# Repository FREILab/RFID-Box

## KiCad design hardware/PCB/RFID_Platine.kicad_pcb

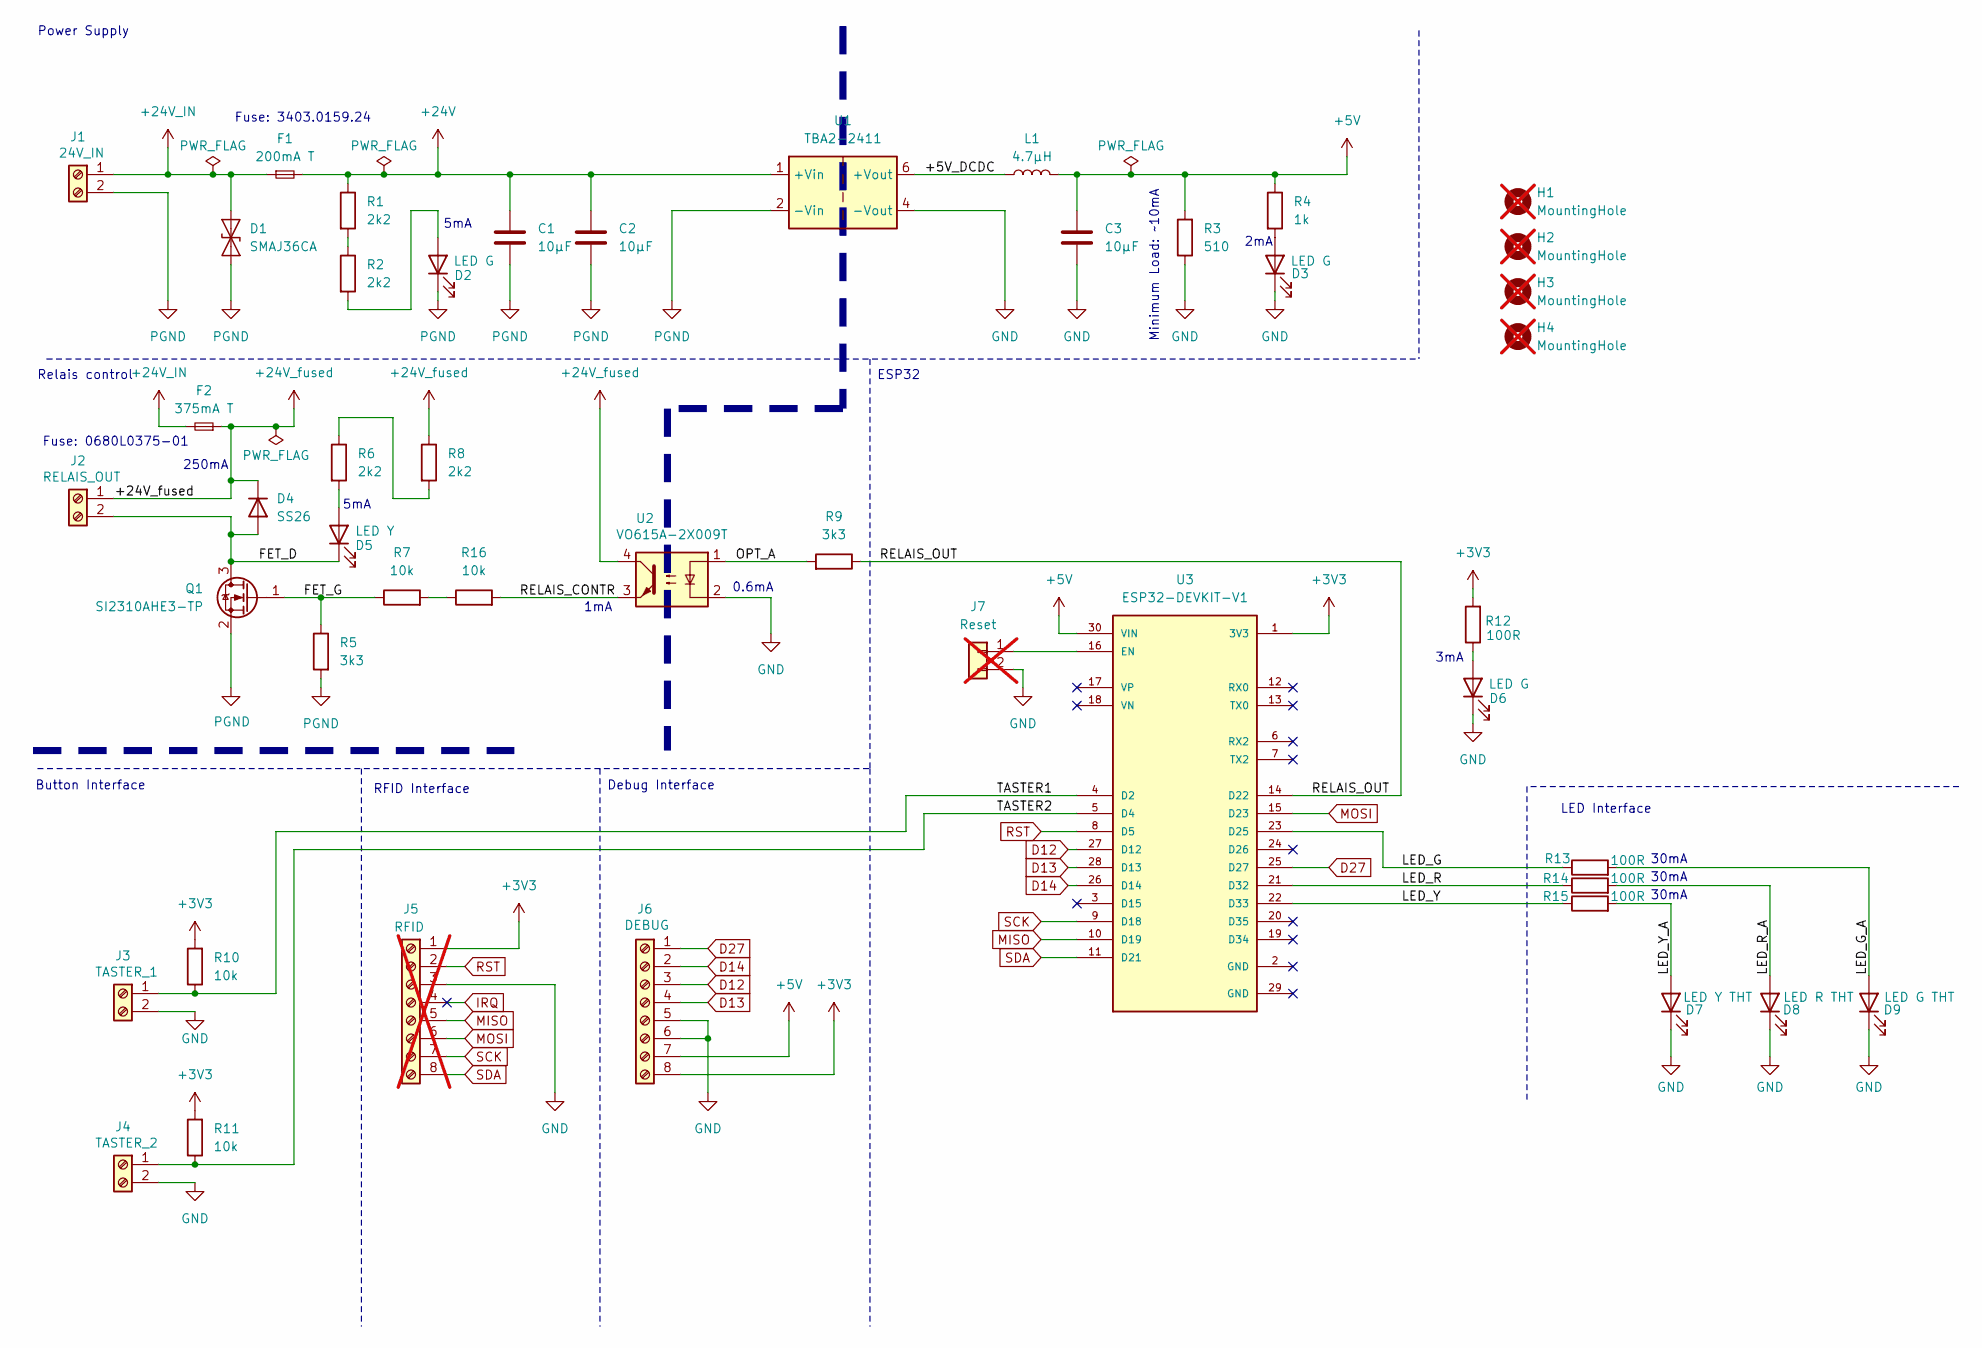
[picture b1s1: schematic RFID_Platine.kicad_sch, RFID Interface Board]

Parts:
C1, C2, C3: 10µF; C_0805_2012Metric; Voltage Rating 50V; Digikey 490-GRM21BR61H106KE43KCT-ND
D1: SMAJ36CA; D_SMA; Digikey SMAJ36CA-TPMSCT-ND
D2, D3, D6: LED G; LED_0603_1608Metric; Digikey 160-1183-1-ND
D4: SS26; D_SMA; Digikey SS26-LTPMSCT-ND
D5: LED Y; LED_0603_1608Metric; Digikey 160-1448-1-ND
D7: LED Y THT; LED_D5.0mm_Horizontal_O6.35mm_Z15.0mm; Digikey 1516-1362-ND
D8: LED R THT; LED_D5.0mm_Horizontal_O6.35mm_Z15.0mm; Digikey 1516-1359-ND
D9: LED G THT; LED_D5.0mm_Horizontal_O6.35mm_Z15.0mm; Digikey 1516-1364-ND
F1: 200mA T; Fuse_Schurter_UMZ250; Digikey 486-4658-1-ND
F2: 375mA T; Fuse_Littelfuse-NANO2-451_453; Digikey 5923-0680L0375-01CT-ND
H1, H2, H3, H4: MountingHole; MountingHole_4mm; not fitted
J1: 24V_IN; TerminalBlock_Phoenix_PT-1,5-2-3.5-H_1x02_P3.50mm_Horizontal; Digikey 277-1721-ND
J2: RELAIS_OUT; TerminalBlock_Phoenix_PT-1,5-2-3.5-H_1x02_P3.50mm_Horizontal; Digikey 277-1721-ND
J3: TASTER_1; TerminalBlock_Phoenix_PT-1,5-2-3.5-H_1x02_P3.50mm_Horizontal; Digikey 277-1721-ND
J4: TASTER_2; TerminalBlock_Phoenix_PT-1,5-2-3.5-H_1x02_P3.50mm_Horizontal; Digikey 277-1721-ND
J5: RFID; PinHeader_1x08_P2.54mm_Vertical; not fitted
J6: DEBUG; PinHeader_1x08_P2.54mm_Vertical
J7: Reset; PinHeader_1x02_P2.54mm_Vertical; not fitted
L1: 4.7µH; L_Chilisin_BMRB00060650; Digikey 445-174746-1-ND
Q1: SI2310AHE3-TP; SOT-23; Digikey 353-SI2310AHE3-TP-ND
R1, R2, R6, R8: 2k2; R_0603_1608Metric; Power Rating 100mW; Digikey 13-RC0603FR-132K2LCT-ND
R3: 510; R_0603_1608Metric; Power Rating 100mW; Digikey 311-510HRCT-ND
R4: 1k; R_0603_1608Metric; Power Rating 100mW; Digikey 311-1.00KHRCT-ND
R5, R9: 3k3; R_0603_1608Metric; Power Rating 100mW; Digikey 311-3.30KHRCT-ND
R7, R10, R11, R16: 10k; R_0603_1608Metric; Power Rating 100mW; Digikey 311-10.0KHRCT-ND
R12, R13, R14, R15: 100R; R_0805_2012Metric; Power Rating 125mW; Digikey 311-100CRCT-ND
U1: TBA2-2411; Converter_DCDC_TRACO_TBA2-xxxx_Single_THT; Digikey 1951-3441-ND
U2: VO615A-2X009T; DIP-4_W8.89mm_SMDSocket_LongPads; Digikey VO615A-2X009TCT-ND
U3: ESP32-DEVKIT-V1; MODULE_ESP32_DEVKIT_V1; PARTREV N/A

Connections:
+3V3: J5.1, J6.8, R10.2, R11.2, R12.2, U3.1 (3V3)
+5V: C3.1, J6.7, L1.2, R3.2, R4.1, U3.30 (VIN)
+24V: C1.1, C2.1, F1.2, R1.1, U1.1 (+Vin)
+24V_IN: D1.2 (A2), F1.1, F2.2, J1.1
+24V_fused: D4.1 (K), F2.1, J2.1, R8.1, U2.4
/+5V_DCDC: L1.1, U1.6 (+Vout)
/FET_D: D4.2 (A), D5.1 (K), J2.2, Q1.3 (D)
/FET_G: Q1.1 (G), R5.1, R7.1
/LED_G: R13.1, U3.23 (D25)
/LED_G_A: D9.2 (A), R13.2
/LED_R: R14.1, U3.21 (D32)
/LED_R_A: D8.2 (A), R14.2
/LED_Y: R15.1, U3.22 (D33)
/LED_Y_A: D7.2 (A), R15.2
/OPT_A: R9.2, U2.1
/RELAIS_CONTR: R16.2, U2.3
/RELAIS_OUT: R9.1, U3.14 (D22)
/TASTER1: J3.1, R10.1, U3.4 (D2)
/TASTER2: J4.1, R11.1, U3.5 (D4)
D12: J6.3, U3.27 (D12)
D13: J6.4, U3.28 (D13)
D14: J6.2, U3.26 (D14)
D27: J6.1, U3.25 (D27)
GND: C3.2, D3.1 (K), D6.1 (K), D7.1 (K), D8.1 (K), D9.1 (K), J3.2, J4.2, J5.3, J6.5, J6.6, J7.2, R3.1, U1.4 (-Vout), U2.2
IRQ: J5.4
MISO: J5.5, U3.10 (D19)
MOSI: J5.6, U3.15 (D23)
unnamed: D2.2 (A), R2.2
unnamed: D3.2 (A), R4.2
unnamed: D5.2 (A), R6.2
unnamed: D6.2 (A), R12.1
unnamed: J7.1, U3.16 (EN)
unnamed: R1.2, R2.1
unnamed: R6.1, R8.2
unnamed: R7.2, R16.1
PGND: C1.2, C2.2, D1.1 (A1), D2.1 (K), J1.2, Q1.2 (S), R5.2, U1.2 (-Vin)
RST: J5.2, U3.8 (D5)
SCK: J5.7, U3.9 (D18)
SDA: J5.8, U3.11 (D21)

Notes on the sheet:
2mA
30mA
Fuse: 3403.0159.24
RFID Interface
LED Interface
5mA
0.6mA
Relais control
1mA
3mA
Debug Interface
Button Interface
250mA
ESP32
Power Supply
Fuse: 0680L0375-01
Minimum Load: ~10mA

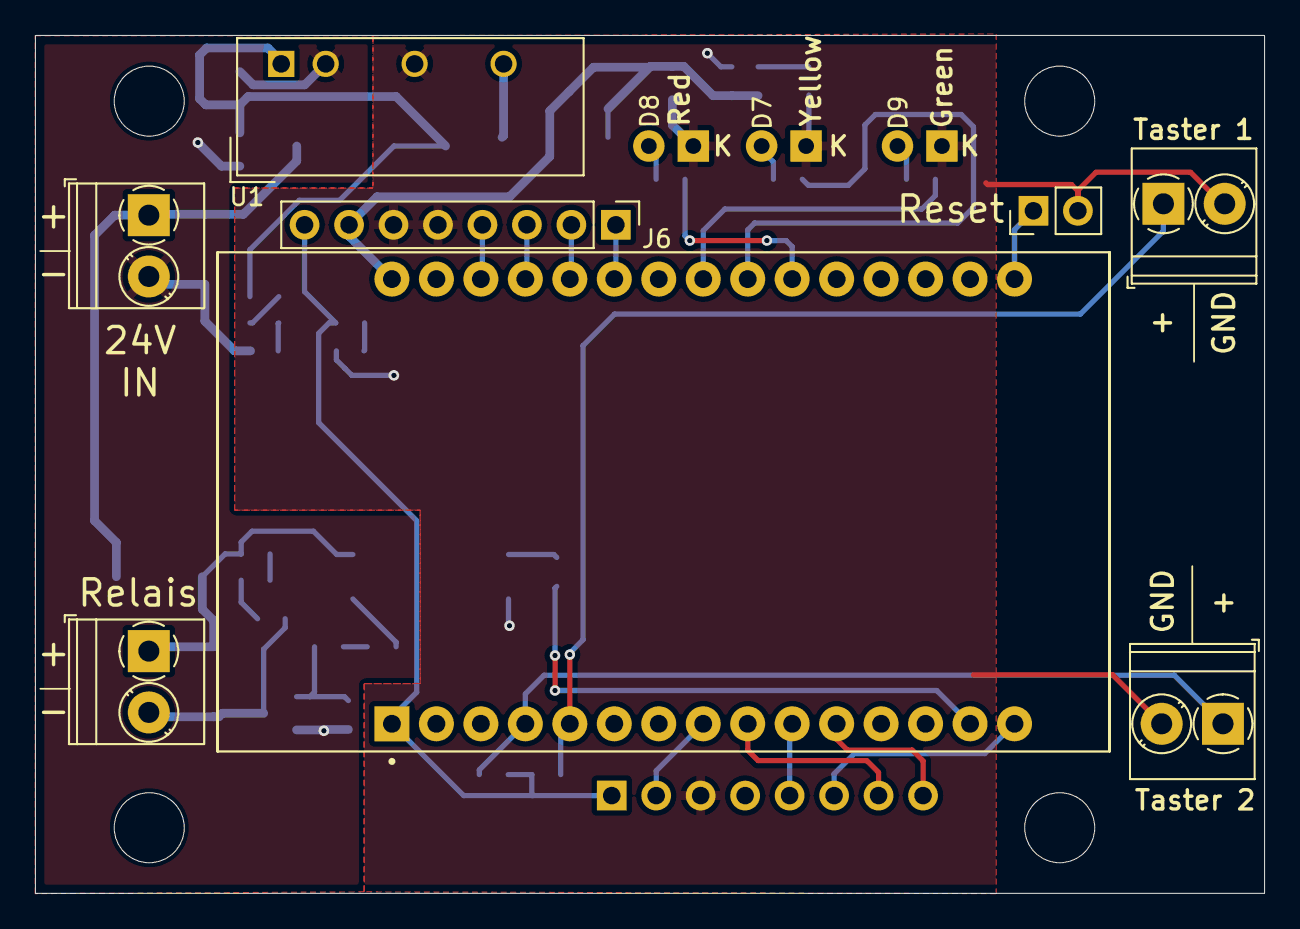
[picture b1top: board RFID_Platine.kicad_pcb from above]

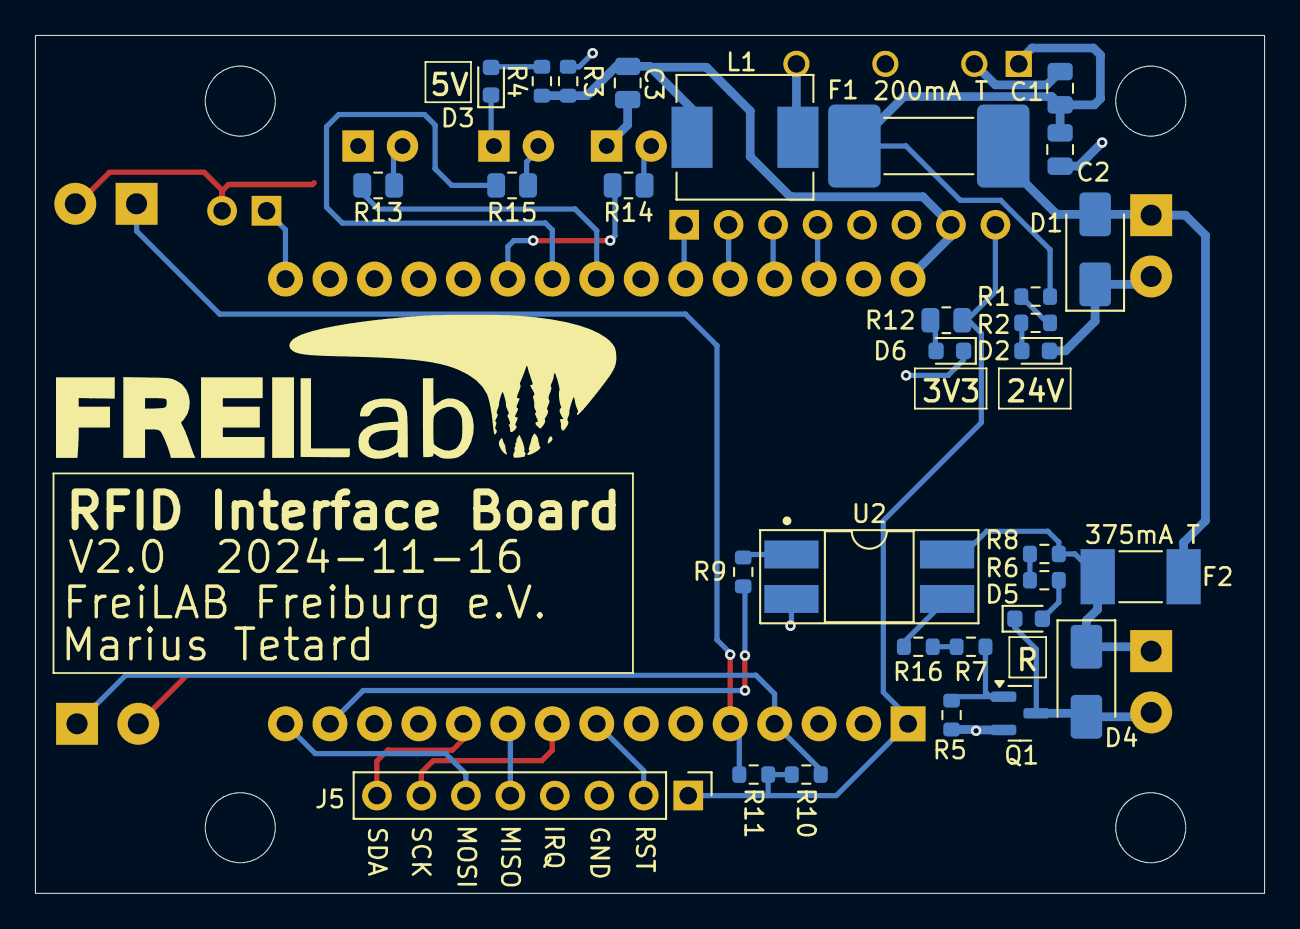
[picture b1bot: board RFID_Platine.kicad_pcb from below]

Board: 2 copper layers, 70.2 x 49.0 mm, 46 parts (31 on the bottom side), 38 nets.

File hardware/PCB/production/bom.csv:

Designator,Footprint,Quantity,Value,LCSC Part #
"C1, C2, C3",0805,3,10µF,C440198
D1,D_SMA,1,SMAJ36CA,C908830
"D2, D3, D6",0603,3,LED G,C22371298
D4,D_SMA,1,SS26,C5350986
D5,0603,1,LED Y,C74343
D7,LED_D5.0mm_Horizontal_O6.35mm_Z15.0mm,1,LED Y THT,
D8,LED_D5.0mm_Horizontal_O6.35mm_Z15.0mm,1,LED R THT,
D9,LED_D5.0mm_Horizontal_O6.35mm_Z15.0mm,1,LED G THT,
F1,Fuse_Schurter_UMZ250,1,200mA T,
F2,Fuse_Littelfuse-NANO2-451_453,1,375mA T,
J1,"TerminalBlock_Phoenix_PT-1,5-2-3.5-H_1x02_P3.50mm_Horizontal",1,24V_IN,
J2,"TerminalBlock_Phoenix_PT-1,5-2-3.5-H_1x02_P3.50mm_Horizontal",1,RELAIS_OUT,
J3,"TerminalBlock_Phoenix_PT-1,5-2-3.5-H_1x02_P3.50mm_Horizontal",1,TASTER_1,
J4,"TerminalBlock_Phoenix_PT-1,5-2-3.5-H_1x02_P3.50mm_Horizontal",1,TASTER_2,
J6,PinHeader_1x08_P2.54mm_Vertical,1,DEBUG,
L1,L_Chilisin_BMRB00060650,1,4.7µH,C5189938
Q1,SOT-23,1,SI2310AHE3-TP,C5243799
"R1, R2, R6, R8",0603,4,2k2,C2907117
"R10, R11, R16, R7",0603,4,10k,C15401
"R12, R13, R14, R15",0805,4,100R,C103909
R3,0603,1,510,C2907048
R4,0603,1,1k,C21190
"R5, R9",0603,2,3k3,C22978
U1,Converter_DCDC_TRACO_TBA2-xxxx_Single_THT,1,TBA2-2411,
U2,DIP-4_W8.89mm_SMDSocket_LongPads,1,VO615A-2X009T,C5369220
U3,MODULE_ESP32_DEVKIT_V1,1,ESP32-DEVKIT-V1,

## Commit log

2024-01-20 Add mashine id.
2025-02-08 add hw files
2025-04-06 move to sub folder
